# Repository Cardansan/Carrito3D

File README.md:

# Repositorio de flujos de Node-RED para VAPRPi-RED
## Pasos para la instalación del software
### 1) Instalar Node-RED.
Descargar la última versión de Node-RED para la imagen de Raspbian que usará la raspberry. Habilitar el servicio para que Node-RED corra en cada encendido.
### 2) Liberar el mayor espacio posible para ejecutar Node-RED.
Ir a /lib/systemd/system/nodered.service para editar el max-old-space a una cantidad razonable. Se ha probado con 1024 exitosamente. Detener, ejecutar "sudo systemctl daemon-reload" y volver a correr Node-RED.
### 3) Habilitar la conexión a la cámara de la raspberry.
Desde raspi-config habilitar la cámara. Recuerda que después de esto necesitarás reiniciar la rasp (puedes hacerlo después del siguiente paso).
### 4) Configuración previa para el control de servos.
Ejecutar el comando:
```bash
$ sudo apt-get install pigpio
```

Modificar el documento /etc/rc.local y añadir la línea "/usr/bin/pigpiod" al final del archivo, justo antes del último "exit 0". 
Se verá así:
```bash
/usr/bin/pigpiod
exit 0
```
Requiere reinicio de la Raspberry. 

### 5) Activar la transmisión y recolección de video via web.
Instala Git, probablemente no venga por default en el Raspberry OS.
```bash
$ sudo apt update
$ sudo apt install git
```

Actualizar o instalar php (usar al menos la versión 7.3) 
```bash
$ sudo apt-get install php7.3
```
Nota: Si se pausa el último comando y quedan dos puntos ":" oprimir "q" para continuar.

(Antes para instalar php en la versión Stretch de Raspbian se usó el manual como se describe en el archivo Php_Install_Instructions hallado en este repo.)

Instalar RPi-Cam-Web-Interface tal como se menciona en la página: https://elinux.org/RPi-Cam-Web-Interface#Installation_Instructions
Nota: Borrar el "html" de la configuración al instalar.

```bash
$ git clone https://github.com/silvanmelchior/RPi_Cam_Web_Interface.git
$ cd RPi_Cam_Web_Interface
$./install.sh
```

### 6) Importar los flujos.
Desde Node-RED importar los flujos hallados en este repositorio. 
### 7) Instalar los nodos faltantes.
No todos los nodos que se usarán vienen en la instalación default de Node-RED, así que se debe revisar cuáles se necesitan instalar desde Manage Palette.
### 8) Desplegar los flujos.
Esto hará que se empiecen a ejecutar siempre que se encienda la raspberry y la interfaz del vehículo deberá de aparecer en el Dashboard de Node-RED con todo y la transmisión del video en vivo.

## Notas
- Por la duración de las descargas e instalaciones, dura aproximadamente entre una y dos horas el proceso completo.
- Otra forma para que la Raspberry Zero se vuelva transmisora de video: https://chriscarey.com/blog/2017/04/30/achieving-high-frame-rate-with-a-raspberry-pi-camera-system/
(Tiene delay de 3 a 5 seg)
- Se presentó varias veces el error "mmal: mmal_vc_component_enable: failed to enable component: ENOSPC" solucionado con el comando "sudo pkill raspimjpeg" o fijándose que el módulo de la cámara estuviera bien conectado.
- Para que funcionaran los servos de manera correcta se utilizaron los nodos de aquí https://flows.nodered.org/node/node-red-node-pi-gpiod, tomar en cuenta que tienes que modificar el documento /etc/rc.local y añadir la línea "sudo pigpiod" antes del último "exit 0". Esto trae unas vulnerabilidades (puerto TCP 8888) que se pueden atender según el mismo enlace.

## Enlaces relacionados
- Raspberry Pi Zero en modo OTG (para SSH): https://caron.ws/diy-cartes-microcontroleurs/raspberrypi/pi-zero-otg-ethernet/
- Captive Portals en Raspberry Pi: https://pimylifeup.com/raspberry-pi-captive-portal/
- AP y Station Mode usando Docker: https://github.com/txn2/txwifi
- Captive Portals usando Docker: https://github.com/cjimti/iotweb
- Access Point y Managed Mode Wifi en RPi (No siempre confiable): https://blog.thewalr.us/2017/09/26/raspberry-pi-zero-w-simultaneous-ap-and-managed-mode-wifi/
- Script AP del enlace anterior: https://github.com/lukicdarkoo/rpi-wifi
- Install and configure Pigpiod: https://github.com/guymcswain/pigpio-client/wiki/Install-and-configure-pigpiod

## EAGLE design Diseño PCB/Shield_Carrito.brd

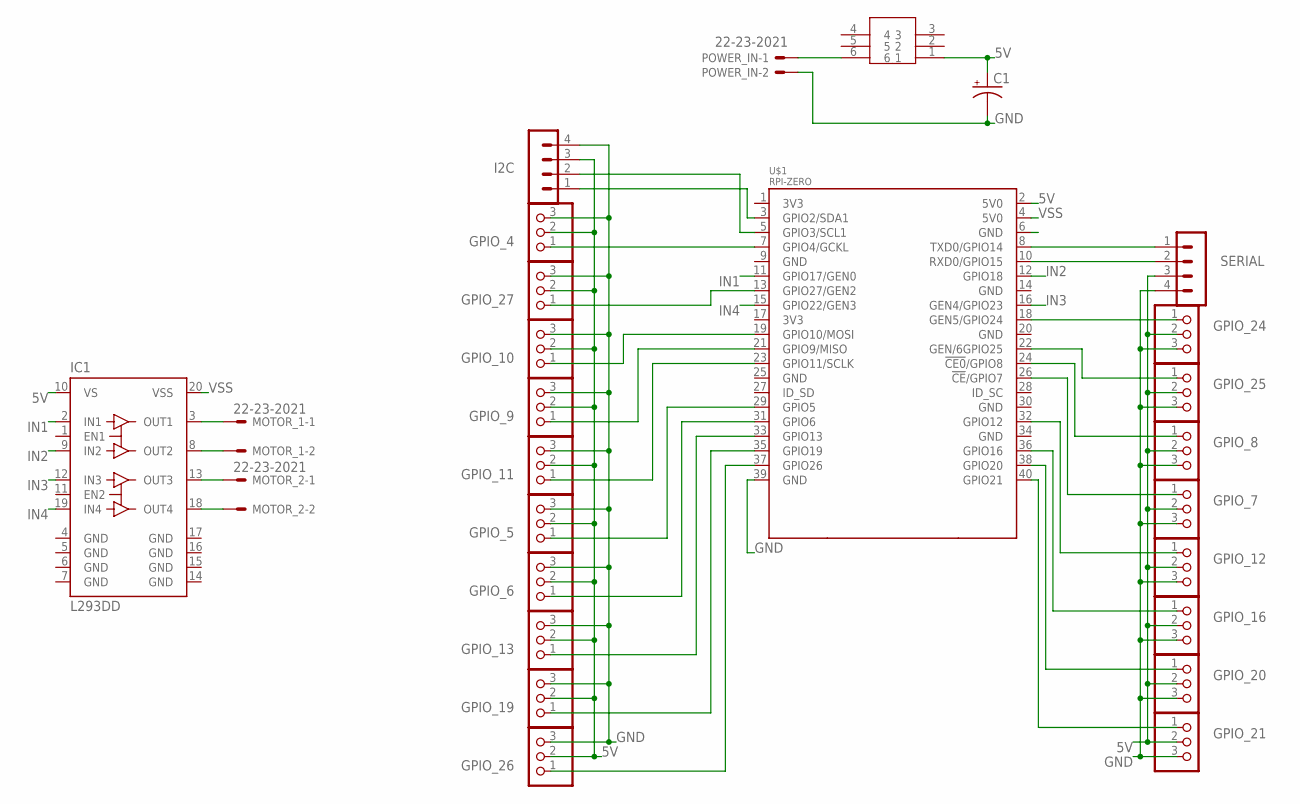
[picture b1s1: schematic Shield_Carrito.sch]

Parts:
C1: CPOL-USE2,5-6E; E2,5-6E
GPIO_4, GPIO_5, GPIO_6, GPIO_7, GPIO_8, GPIO_9, GPIO_10, GPIO_11, GPIO_12, GPIO_13, GPIO_16, GPIO_19, GPIO_20, GPIO_21, GPIO_24, GPIO_25, GPIO_26, GPIO_27: PINHD-1X3; 1X03
I2C: MA04-1
IC1: L293DD; SO20
MOTOR_1, MOTOR_2: 22-23-2021
POWER_IN: 22-23-2021
SERIAL: MA04-1
U$1: RPI-ZERO; RASPBERRYPI_BASTELSTUBE_V13_RASPI_BOARD_B+_FULL
U$2: PUSH_SWITCH_8X8

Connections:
5V: C1.+, GPIO_4.2, GPIO_5.2, GPIO_6.2, GPIO_7.2, GPIO_8.2, GPIO_9.2, GPIO_10.2, GPIO_11.2, GPIO_12.2, GPIO_13.2, GPIO_16.2, GPIO_19.2, GPIO_20.2, GPIO_21.2, GPIO_24.2, GPIO_25.2, GPIO_26.2, GPIO_27.2, I2C.3, IC1.10 (VS), SERIAL.3, U$1.2 (5V0), U$2.1
GND: C1.-, GPIO_4.3, GPIO_5.3, GPIO_6.3, GPIO_7.3, GPIO_8.3, GPIO_9.3, GPIO_10.3, GPIO_11.3, GPIO_12.3, GPIO_13.3, GPIO_16.3, GPIO_19.3, GPIO_20.3, GPIO_21.3, GPIO_24.3, GPIO_25.3, GPIO_26.3, GPIO_27.3, I2C.4, IC1.4 (GND), IC1.5 (GND), IC1.6 (GND), IC1.7 (GND), IC1.14 (GND), IC1.15 (GND), IC1.16 (GND), IC1.17 (GND), POWER_IN.2, SERIAL.4, U$1.6 (GND), U$1.39 (GND)
IN1: IC1.2 (IN1), U$1.11 (GPIO17/GEN0)
IN2: IC1.9 (IN2), U$1.12 (GPIO18)
IN3: IC1.12 (IN3), U$1.16 (GEN4/GPIO23)
IN4: IC1.19 (IN4), U$1.15 (GPIO22/GEN3)
unnamed: GPIO_26.1, U$1.37 (GPIO26)
unnamed: GPIO_24.1, U$1.18 (GEN5/GPIO24)
unnamed: GPIO_25.1, U$1.22 (GEN/6GPIO25)
unnamed: GPIO_12.1, U$1.32 (GPIO12)
unnamed: GPIO_16.1, U$1.36 (GPIO16)
unnamed: GPIO_20.1, U$1.38 (GPIO20)
unnamed: GPIO_21.1, U$1.40 (GPIO21)
unnamed: GPIO_8.1, U$1.24 (!CE0!/GPIO8)
unnamed: GPIO_7.1, U$1.26 (!CE!/GPIO7)
unnamed: POWER_IN.1, U$2.6
unnamed: IC1.13 (OUT3), MOTOR_2.1
unnamed: IC1.18 (OUT4), MOTOR_2.2
unnamed: IC1.3 (OUT1), MOTOR_1.1
unnamed: GPIO_27.1, U$1.13 (GPIO27/GEN2)
unnamed: GPIO_10.1, U$1.19 (GPIO10/MOSI)
unnamed: GPIO_11.1, U$1.23 (GPIO11/SCLK)
unnamed: GPIO_9.1, U$1.21 (GPIO9/MISO)
unnamed: GPIO_5.1, U$1.29 (GPIO5)
unnamed: GPIO_6.1, U$1.31 (GPIO6)
unnamed: GPIO_13.1, U$1.33 (GPIO13)
unnamed: GPIO_19.1, U$1.35 (GPIO19)
unnamed: GPIO_4.1, U$1.7 (GPIO4/GCKL)
unnamed: IC1.8 (OUT2), MOTOR_1.2
unnamed: I2C.2, U$1.5 (GPIO3/SCL1)
unnamed: I2C.1, U$1.3 (GPIO2/SDA1)
unnamed: SERIAL.1, U$1.8 (TXD0/GPIO14)
unnamed: SERIAL.2, U$1.10 (RXD0/GPIO15)
VSS: IC1.20 (VSS), U$1.4 (5V0)

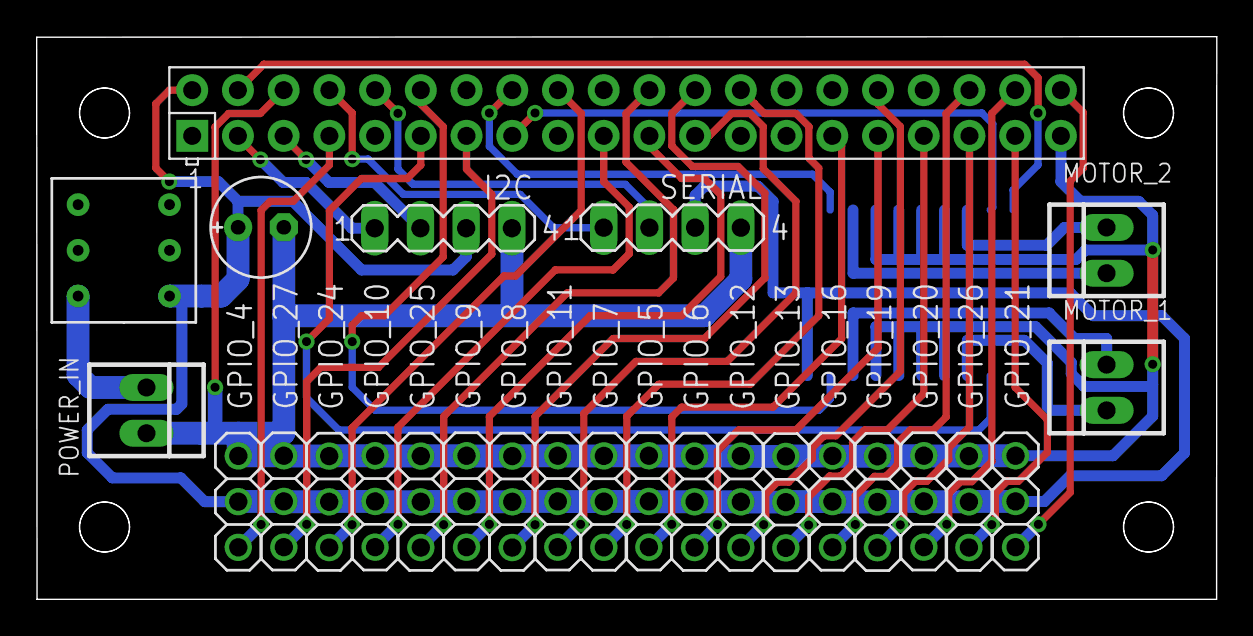
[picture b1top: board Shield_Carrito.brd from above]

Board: 2 copper layers, 65.6 x 31.3 mm, 27 parts (1 on the bottom side), 34 nets.

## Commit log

2019-07-01 Inicio y prueba motores
2019-07-02 Control de motores por puente H
2019-07-04 Control de Servos y botones bonitos
2019-07-04 Control de Servos y botones bonitos 2
2019-07-05 Control de todos los servos, limpieza de orden nodos
2019-07-06 Pruebas de fotos
2019-07-08 Botones formato
2019-07-09 video tiempo real
2019-07-09 Se integra el video en tiempo real a Dashboard
2019-07-11 Pruebas botones
2019-07-15 Botones momentáneos
2019-07-22 Carrito controlado por UI y con visión por WiFi
2019-09-21 Diagrama de conexiones
2019-09-21 Correcciones de conexiones.
2019-09-21 conexiones
2019-09-28 Instrucciones PHP
2019-09-28 Cámara deshabilitada.
2019-09-28 corrección conexiones
2019-10-10 Shield para el proyecto del carrito FPV-v2
    Diseño del shield para servomotores, puente H (L293DD) y conexión para I2C y serial.
2019-12-09 Sólo flujos aquí.
2020-01-25 Revisión Carlos: lijado sensor, corrección Autónomo, guardar red WiFi
2020-02-29 Pruebas Google Home
2020-05-07 se agregaron las funcionalidades de telegram y compartir el dashboard remotamente
2020-05-09 Prueba
2020-05-09 Prueba2 -C
2020-05-14 Update README.md
    Para activar los pines por medio de pigpiod el archivo rc.local se envia el comando "sudo pigpiod"
2020-05-14 se elimino el nodo "esto no es nada"
2020-05-14 agregue el bot de RedFire
2020-05-21 Estoy agregando variables para poder ajustar el centro y los limites de movimiento del volante, así como la personalización de los pines de los motores y servo para el caso en específico de esta plac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
2020-05-21 Los botones vibran
2020-05-21 Mandar foto a Telegram
2020-05-21 probando push (borrar archivo)
2020-05-22 previo a practica 22 mayo
2020-07-30 (GrinGreen) Vibración, Límites Der e Izq
2020-07-30 (GrinGreen III) Vibración, Límites Der e Izq
2020-07-30 Delete flow.json
    Borré prueba
2020-07-30 Delete flow_cred.json
    Borré prueba
2020-07-30 Pin de volante corregido
2020-07-30 Blacky Update
2020-08-02 Se duplicó una señal para el volante de RedFire, se agregó el pin 40
2020-08-02 Agrege mqtt chat y nueva ip de google home
2020-08-02 El chat por mqtt ya tiene voz
2020-08-02 El chat deja registro ahora en telegram
2020-08-03 Colores dinámicos, arranque
2020-08-03 Cambio botones
2020-08-04 Poderes cambian de color
2020-08-04 Se agregó el canal de conteo regresivo, se manda el link de ngrok cuando sea necesario, se aguregáron pruebas QR
2020-08-04 agregué el ngrok para hacer ssh
2020-08-05 Filtro null
2020-08-06 Empty filter + Tópicos Mqtt por variables
2020-08-06 Avances Recibimos Misil
2020-08-06 corregir volante GrinGreen >:[
2020-08-06 pronunciar bien Gringrin
2020-08-06 Se borran los mensajes enviados en el espacio del chat
2020-08-06 Separar Apagado y Reinicio
2020-08-06 añado comando de telegram para apagado
2020-08-06 Recibir poderes ya hace algo!
2020-08-06 Corregir apagar
2020-08-06 Usar bolt no te ataca a ti mismo
2020-08-07 Agregué el token del bot como variable enviroment y se agregró en el archivo de settings.js
2020-08-07 Fix reboot
2020-08-08 Tabs escondidas, modo experto escondido
2020-08-08 Creo que ya quedó poderes
2020-08-08 elimino autoauth
2020-08-08 Efectos luz, corrección null Misil
2020-08-28 HTML color Picker, Enable Autonomo, Fix tabs
2020-08-29 Pruebas Uptime para no enviar viejos enlaces
2020-08-29 Pruebas Uptime II
2020-08-29 Prueba uptime en segundos
2020-08-29 Depuración Poderes y QR
2020-09-02 Quitar mensaje Uptime
2020-09-07 cambié el comando para verificar la IP, ahora con hostname -I
2020-09-08 Se cambió a formulario el cambio de red Wifi sin exponer la red ni contraseña
2020-09-08 Agregué una entrada de texto para cambiar el nombre del Vapri y envio el comando para actualizarlo en la camara
2020-09-08 Se agregó espacio para personalizar el bot token y se reinicia node red para surtir efecto
2020-09-09 Se agragaron botones y ventanas emergentes para confirmar cambios en token y red, así como mostrar la red wifi conectada
2020-09-09 El nombre del Vapri se transforma en el nombre de la red AP, así como el nombre a mostrar en la pestaña del Dashboard y en la cámara, falta personalizarlo tambien en el runtime editor
2020-09-09 corregí el caso para cuando se cancela el cambio de nombre
2020-09-09 Se personaliza tambien el nombre en el runtime editor. Falta agregar la entrada en dasboard para el chat id del grupo de telegram para la torre de control. así como poner en variable env el topico pa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
2020-09-09 Se agregó espacio para seleccionar el Chat ID para que ese sea el grupo a donde se envían los mensajes y de donde sale quien es control
2020-10-10 Incluyo Modo Demo
2020-10-10 Filtrado de mensajes externos
2020-11-07 Corrección Pregunta Telegram, creo ssh no jala, pruebas auto-disable camara tiran ngrok.
2020-11-07 Ejecutar Script de AP en el primer inicio, avisa por el VapriChat el estado
2020-11-25 avances correción VapriNameCaps
2020-12-02 Quité el nodo de checar si hay conectado alguien en la camara para mostrar video
2020-12-02 Ajustes de admin y funciona avanzada deshabilitadas.
2020-12-03 Corrección Bolt Infinito
2020-12-03 Misil nombre ya no se confunde por mayúsculas (Hay error en el avance después)
2020-12-03 Corrección "Bajo Ataque Misil" motores arrancaban en automático si te atacaban estando quietx
2020-12-04 Modo Exploración aparentemente listo, detecta las 4 pistas sin repetir y avisa cuando se han juntado todas por el chat
2020-12-04 Modo Exploración también manda mensaje por MQTT al Chat
2021-02-19 Actualización instrucciones de acuerdo a Buster, ya no Stretch
2021-03-27 Borrar Nodos sin Tab ID
2021-04-05 Crea las var ENV de Telegram si es el primer inicio de NR en una nueva SD
2021-04-05 Crea variables de limitDer e Izq en primer encendido de tarjeta SD
2021-04-05 Reactivar cámara
2021-04-05 Iniciar gpiod y script cámara (¿se ocupan de verdad?)
2021-04-13 Desactivar motores en encendido + Conexión WiFi desde UI con Docker
2021-04-17 Cambios vapri casero - C
2021-06-22 Vapri envía /ip por telegram
